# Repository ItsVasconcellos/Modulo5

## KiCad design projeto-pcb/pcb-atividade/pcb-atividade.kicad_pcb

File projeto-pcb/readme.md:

# Atividade de PCB

A atividade consistiu em criar uma pcb através do software KICAD. Em minha PCB, utilizei de um transistor para permitir ou bloquear a passagem de energia para um led.

## Componentes utilizados

- 2x Connector 1x2
- 1x Raspberry Pi Pico
- 1x Transistor
- 1x Resistor de 10kΩ
- 1x Resistor de 220Ω
- 1x LED simples

## Funcionamento da PCB

O transistor se conecta com a Raspberry Pico através da GPIO16, recebendo um sinal HIGH ou LOW. Com isso, o transistor, passa através do emissor, o output de corrente ou não. Seu emisso está ligado a um conector, que também está ligado a um pino de alimentação de um led.  

## Estrutura de pastas

```bash
projeto-pcb/
├── pcb-atividade/
│   ├── pcb-atividade-backups/    (Contém backups do projeto)
│   │   ├── [Arquivos de backup do projeto]
│   ├── pcb-gbr/                  (Contém todos os arquivos Gerber necessários do projeto)
│   │   ├── [Arquivos Gerber do projeto]
│   ├── fp-info-cache/
│   ├── pcb-atividade.kicad_pcb
│   ├── pcb-atividade.kicad_prl
│   ├── pcb-atividade.kicad_pro
│   ├── pcb-atividade.kicad_sch
│   ├── pcb-atividade.kicad_pcb.lck
│   ├── pcb-atividade.kicad_sch.lck
│   └── readme.md
```

## Projeto PCB

Para facilitar, um glossário do que é cada arquivo e pasta existente no projeto.

- `pcb-atividade/`: Esta pasta contém os arquivos relacionados à atividade do PCB.

  - `pcb-atividade-backups/`: Esta pasta contém backups do projeto PCB.

  - `pcb-gbr/`: Esta pasta contém todos os arquivos Gerber necessários para a fabricação do PCB.

  - `fp-info-cache/`: Esta pasta pode conter informações de cache relacionadas aos footprints utilizados no projeto.

  - `pcb-atividade.kicad_pcb`: Arquivo principal do projeto no formato KiCad PCB, que contém o layout da placa de circuito impresso.

  - `pcb-atividade.kicad_prl`: Arquivo de regras de projeto do KiCad.

  - `pcb-atividade.kicad_pro`: Arquivo de configurações de projeto do KiCad.

  - `pcb-atividade.kicad_sch`: Arquivo principal do esquemático do projeto no formato KiCad.

  - `pcb-atividade.kicad_pcb.lck`: Arquivo de trava associado ao arquivo principal do projeto PCB do KiCad.

  - `pcb-atividade.kicad_sch.lck`: Arquivo de trava associado ao arquivo principal do esquemático do KiCad.

- `readme.md`: Este arquivo contém informações importantes sobre o projeto PCB.

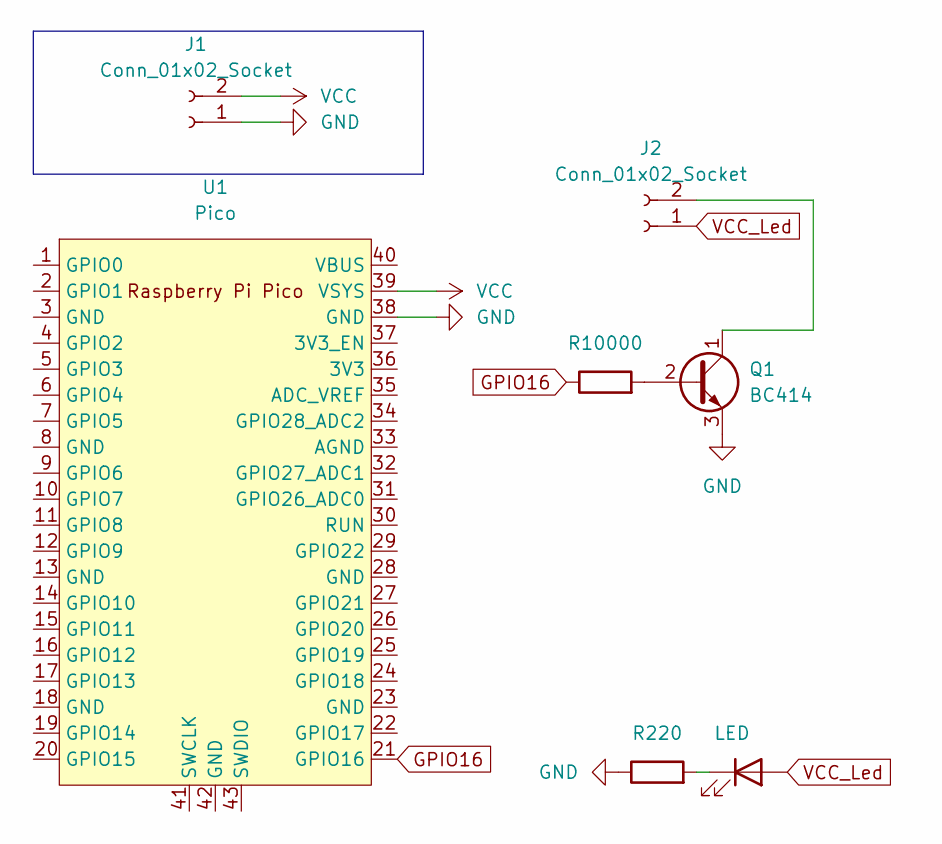
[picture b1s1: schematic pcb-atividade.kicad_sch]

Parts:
D1: LED; LED_D5.0mm
J1: Conn_01x02_Socket; PinHeader_1x02_P1.27mm_Vertical
J2: Conn_01x02_Socket
Q1: BC414; TO-92_Inline
R1: R220; R_Axial_DIN0414_L11.9mm_D4.5mm_P15.24mm_Horizontal
R2: R10000; R_Axial_DIN0414_L11.9mm_D4.5mm_P15.24mm_Horizontal
U1: Pico; RPi_Pico_SMD_TH

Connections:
GND: J1.1, Q1.3 (E), R1.1, U1.38 (GND)
GPIO16: R2.1, U1.21 (GPIO16)
unnamed: D1.1 (K), R1.2
unnamed: J2.2, Q1.1 (C)
unnamed: Q1.2 (B), R2.2
VCC: J1.2, U1.39 (VSYS)
VCC_Led: D1.2 (A), J2.1

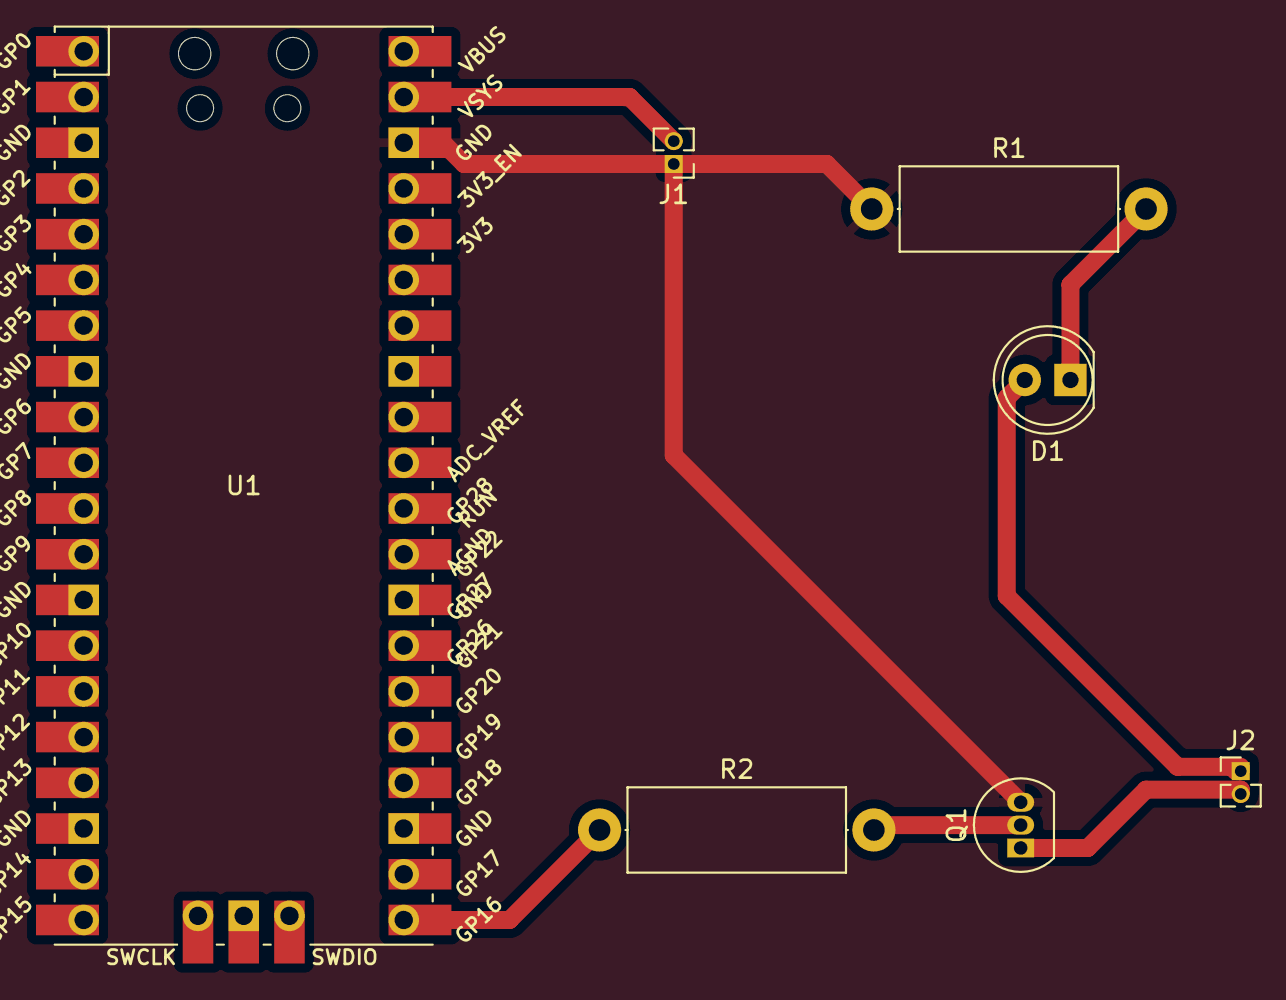
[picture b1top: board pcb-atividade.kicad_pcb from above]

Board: 2 copper layers, 7 parts (0 on the bottom side), 7 nets.

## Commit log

2024-02-19 feat: Adding content for the projects page.
2024-02-19 feat: Adding all the projects to landing page
2024-02-19 chore: adding correct project name
2024-02-19 chore: building the project
2024-02-19 fix: trying to fix git actions deploy
2024-02-19 fix: fix branch error
2024-02-19 fix: path error
2024-02-19 fix: url problem
2024-02-28 feat: robot initial commit
2024-02-28 chore: adding .venv to gitignore
2024-02-28 feat: robot funcionalities
2024-03-02 docs: adding comments on robo.py
2024-03-02 docs: adding read.me to project
2024-03-02 docs: adding video to readme.md
2024-03-31 feat: Atividade PCB
2024-04-01 adjusting files
2024-04-01 adjusting file path
2024-04-01 feat: altering the circuit
2024-04-01 altering file path
2024-04-04 feat: initial commits flask-htmx
2024-04-04 feat:adding endpoints for log
2024-04-04 feat: adding mock from dobotController
2024-04-05 feat: adding htmx to the app
2024-04-05 feat: adding pages and logic for robot
2024-04-05 docs: readme.md
2024-04-05 docs: adding routes
